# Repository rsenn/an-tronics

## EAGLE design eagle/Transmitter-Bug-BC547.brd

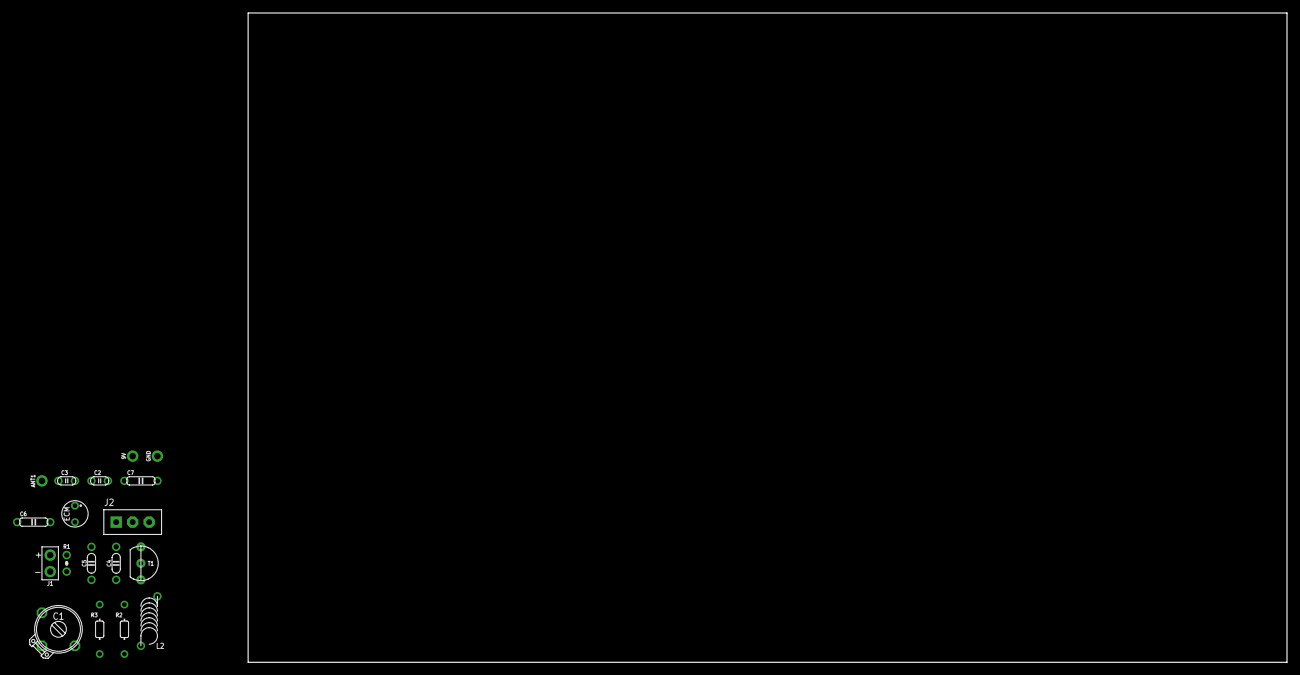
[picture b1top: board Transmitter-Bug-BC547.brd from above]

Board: 2 copper layers, 160.0 x 100.0 mm, 18 parts (0 on the bottom side), 9 nets, no tracks yet.

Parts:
9V: SPAD
ANT1: ANT; SPAD
C1: 1.6-15pF; TRIM-2222-808
C2: 4.7pF; C025-015X024
C3: 1nF; C025-015X024
C4: 1nF; C050-020X036/V
C5: 22nF; C050-020X036/V
C6, C7: 330nF; C050-020X044
ECM: ECM-4
GND: SPAD
J1: SPAD-+
J2: CONN-3P
L2: 1μH; L-04/7V-X
R1: 4.7Ω; 0204/2V
R2: 4.7kΩ; 0202/7-V
R3: 33kΩ; 0202/7-V
T1: BC547; TO92-CBE

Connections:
+UB: 9V.1, C1.3, C5.1, L2.2, R2.1, R3.1
GND: C3.2, C4.2, C5.2, ECM.2, GND.1, J1.1, R1.2
MOD: C4.1, J2.2, R3.2, T1.B
unnamed: C6.2, J2.3
unnamed: ANT1.1, C1.2, C2.1, L2.1, T1.C
unnamed: C2.2, C3.1, R1.1, T1.E
unnamed: C7.2, J2.1
unnamed: C6.1, J1.2
unnamed: C7.1, ECM.1, R2.2

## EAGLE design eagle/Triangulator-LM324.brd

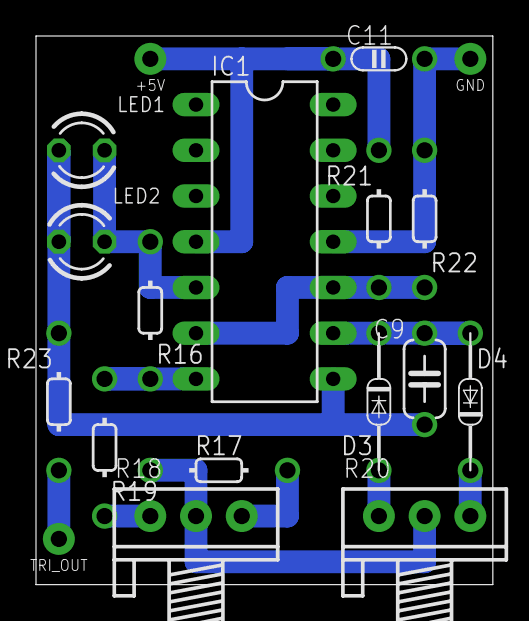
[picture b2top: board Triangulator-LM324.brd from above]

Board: 2 copper layers, 25.4 x 30.5 mm, 18 parts (0 on the bottom side), 13 nets.

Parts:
+5V: VCC; SPAD
C9: 1μF; C050-024X044/V
C11: 100nF; C050-020X036
D3, D4: 1N4148; DO34-7V
GND: GND; SPAD
IC1: LM324; DIL14
LED1, LED2: LED3MM
R16: 47kΩ; 0202/7-V
R17: 4.7kΩ; 0202/7
R18: 10kΩ; POT
R19: 4.7kΩ; 0202/7-V
R20: 100kΩ; POT
R21, R22: 100kΩ; 0202/7-V
R23: 1kΩ; 0202/7-V
TRI_OUT: TRIANGLE; SPAD

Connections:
GND: C11.2, GND.1, IC1.11, R22.1
unnamed: IC1.7, R16.2, R19.1
unnamed: IC1.5, LED1.A, LED2.K, R16.1
unnamed: D3.A, R20.1
unnamed: D4.C, R20.3
unnamed: R17.2, R18.2, R20.2
unnamed: R17.1, R18.3
unnamed: C9.1, D3.C, D4.A, IC1.9
unnamed: R18.1, R19.2
unnamed: C9.2, IC1.8, LED1.K, LED2.A, R23.2
unnamed: R23.1, TRI_OUT.1
unnamed: IC1.6, IC1.10, R21.1, R22.2
VCC: +5V.1, C11.1, IC1.4, R21.2

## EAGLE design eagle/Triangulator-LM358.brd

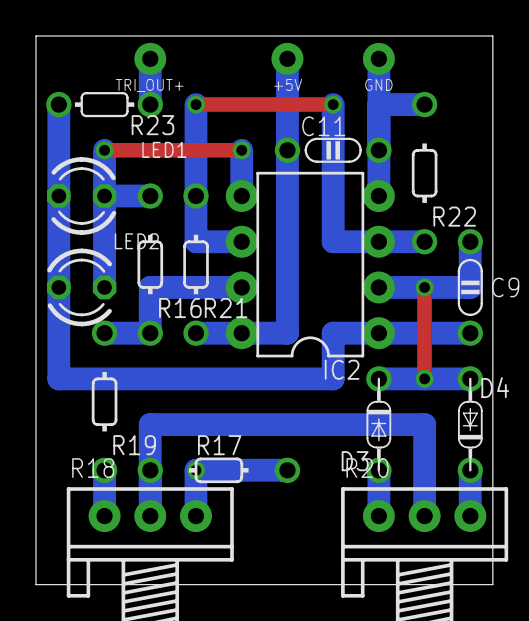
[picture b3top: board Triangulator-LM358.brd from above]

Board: 2 copper layers, 25.4 x 30.5 mm, 18 parts (0 on the bottom side), 13 nets.

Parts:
+5V: VCC; SPAD
C9: 1μF; C050-020X036/V
C11: 100nF; C050-020X036
D3, D4: 1N4148; DO34-5V
GND: GND; SPAD
IC2: LM358N; DIL08
LED1, LED2: LED3MM
R16: 47kΩ; 0202/7-V
R17: 4.7kΩ; 0202/7
R18: 10kΩ; POT
R19: 4.7kΩ; 0202/7-V
R20: 100kΩ; POT
R21, R22: 100kΩ; 0202/7-V
R23: 1kΩ; 0202/5
TRI_OUT+: TRIANGLE; SPAD

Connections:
GND: C11.2, GND.1, IC2.4, R22.1
unnamed: IC2.7, R16.2, R19.1
unnamed: IC2.5, LED1.A, LED2.K, R16.1
unnamed: D3.A, R20.1
unnamed: D4.C, R20.3
unnamed: R17.2, R18.2, R20.2
unnamed: R17.1, R18.3
unnamed: C9.1, D3.C, D4.A, IC2.2
unnamed: R18.1, R19.2
unnamed: C9.2, IC2.1, LED1.K, LED2.A, R23.2
unnamed: R23.1, TRI_OUT+.1
unnamed: IC2.3, IC2.6, R21.1, R22.2
VCC: +5V.1, C11.1, IC2.8, R21.2

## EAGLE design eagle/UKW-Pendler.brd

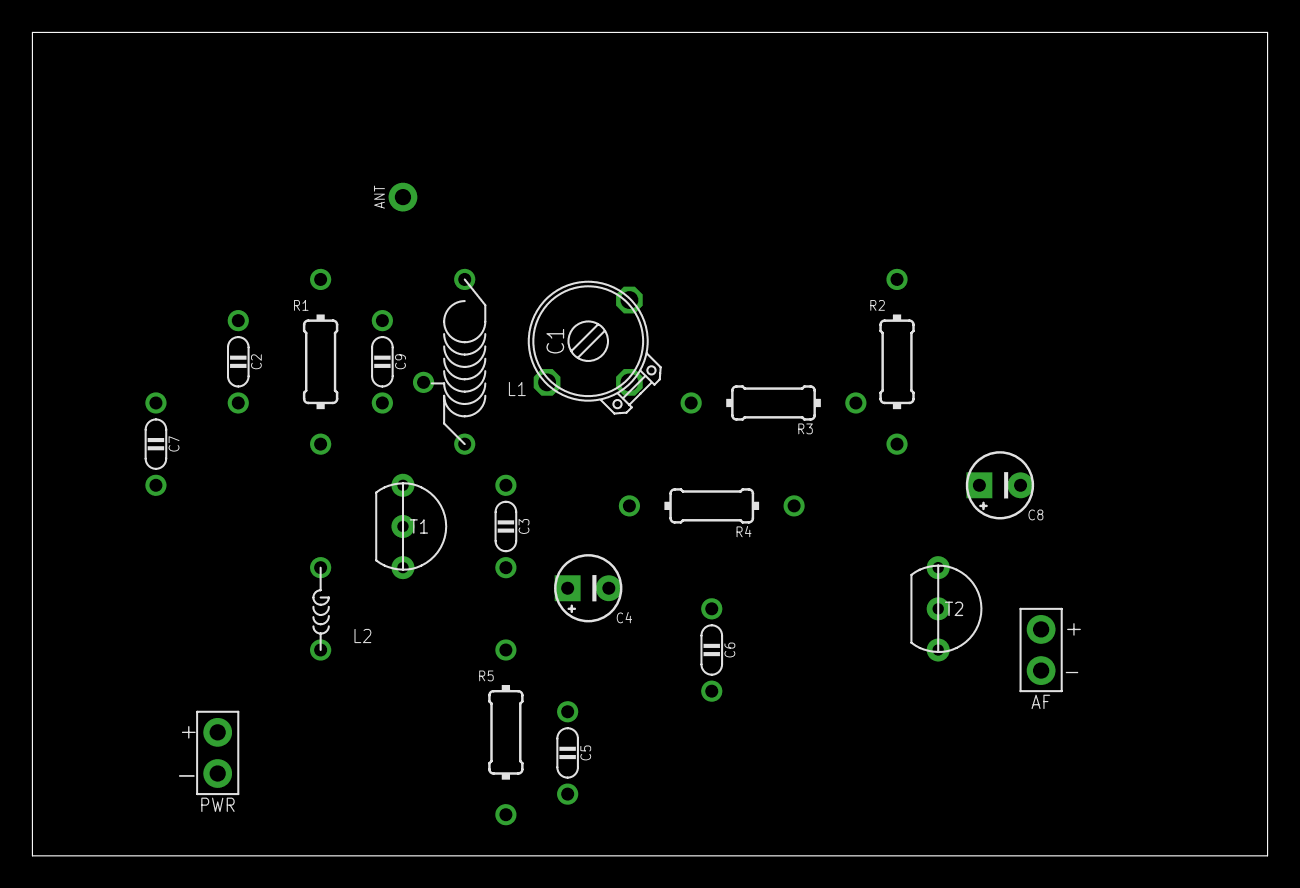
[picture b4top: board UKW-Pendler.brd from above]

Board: 2 copper layers, 76.2 x 50.8 mm, 21 parts (0 on the bottom side), 12 nets, no tracks yet.

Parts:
AF: SPAD+-+-; SPAD+-
ANT: ANT; SPAD
C1: 5-15pF; TRIM-2222-808
C2: 1nF; C050-020X036/V
C3, C5: 27pF; C050-020X036/V
C4: 0.22uF; E2,5-4
C6: 100nF; C050-020X036/V
C7: 10nF; C050-020X036/V
C8: 10uF; E2,5-4
C9: 10pF; C050-020X036/V
J1: PWR-L
L1: L-04/7-TAP1
L2: 4.7uH; L-02/5V
R1: 68k; 0204/10-V
R2, R5: 1k; 0204/10-V
R3: 1M; 0204/10
R4: 10k; 0204/10
T1, T2: BC548B; TO92-CBE

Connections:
GND: AF.1, C5.2, C6.2, C7.2, J1.1, R5.2, T2.E
unnamed: ANT.1, C9.1
unnamed: C3.2, C4.+, L2.2, T1.E
unnamed: C1.2, C3.1, L1.1, T1.C
unnamed: C4.-, R4.2
unnamed: C6.1, R3.2, R4.1, T2.B
unnamed: C5.1, L2.1, R5.1
unnamed: C2.2, R1.2, T1.B
unnamed: C8.+, R2.2, R3.1, T2.C
unnamed: AF.2, C8.-
unnamed: C9.2, L1.T
unnamed: C1.3, C2.1, C7.1, L1.2, R1.1, R2.1

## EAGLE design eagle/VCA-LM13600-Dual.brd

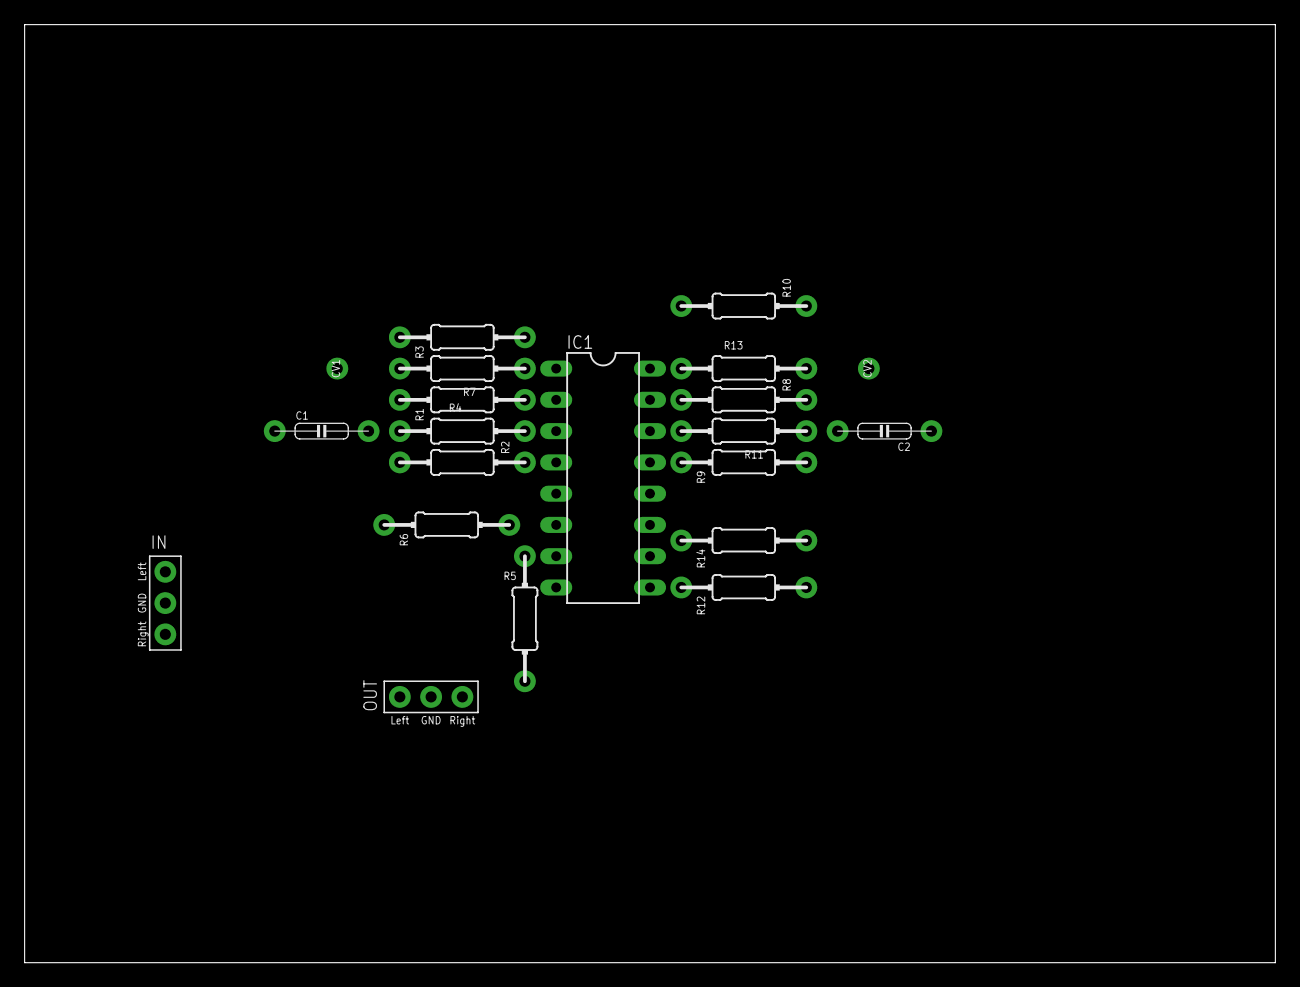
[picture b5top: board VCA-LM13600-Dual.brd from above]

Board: 2 copper layers, 101.6 x 76.2 mm, 21 parts (0 on the bottom side), 21 nets, no tracks yet.

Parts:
C1, C2: 470nF; C075-020X044
CV1, CV2: HPORT; SPAD
IC1: LM13600; DIL16
IN: SAUDIOL-GND-R; SPAD-L-GND-R
OUT: SAUDIOL-GND-R; SPAD-L-GND-R
R1, R8: 10kΩ; 0204/10-V
R2, R3, R9, R10: 470Ω; 0204/10-V
R4, R11: 27kΩ; 0204/10
R5, R12: 33kΩ; 0204/10-V
R6, R14: 4.7kΩ; 0204/10-V
R7, R13: 22kΩ; 0204/10

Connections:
+15V: R1.1, R8.1
-15V: IC1.6, R6.2, R14.2
GND: IN.0, OUT.0, R2.2, R3.1, R5.2, R9.2, R10.1, R12.2
unnamed: IC1.4, R2.1
unnamed: C1.2, R4.1
unnamed: IC1.3, R3.2, R4.2
unnamed: IC1.2, R1.2
unnamed: IC1.1, R7.1
unnamed: IC1.5, IC1.7, R5.1
unnamed: IC1.8, OUT.L, R6.1
unnamed: IC1.13, R9.1
unnamed: IC1.14, R10.2, R11.2
unnamed: IC1.15, R8.2
unnamed: C2.2, R11.1
unnamed: IC1.16, R13.1
unnamed: IC1.9, IC1.12, R12.1
unnamed: IC1.10, OUT.R, R14.1
unnamed: C1.1, IN.L
unnamed: C2.1, IN.R
unnamed: CV1.1, R7.2
unnamed: CV2.1, R13.2

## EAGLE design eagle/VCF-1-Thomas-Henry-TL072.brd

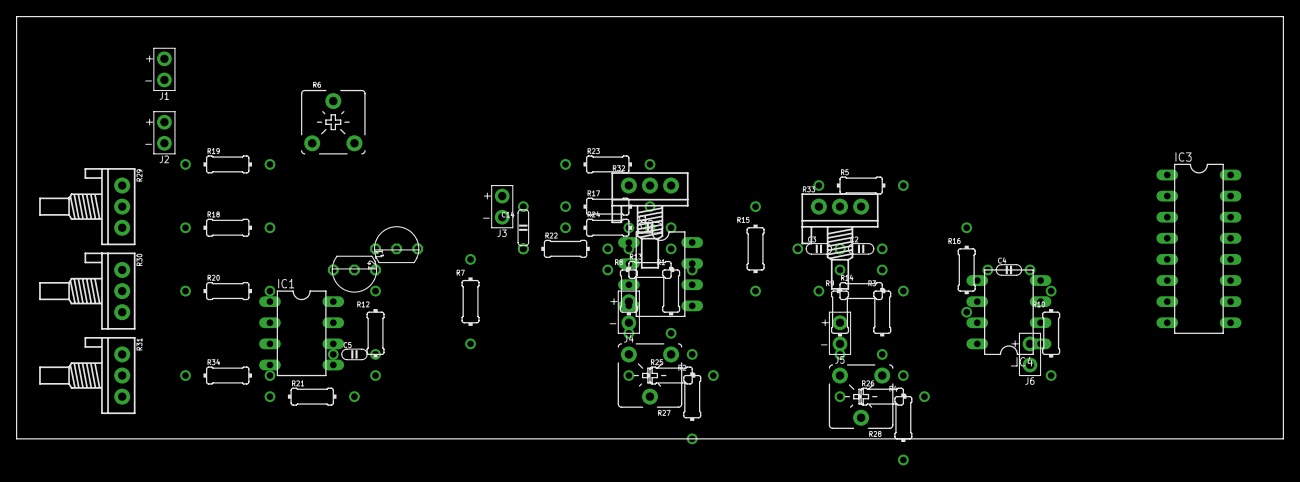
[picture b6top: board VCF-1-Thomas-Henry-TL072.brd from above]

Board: 2 copper layers, 152.4 x 50.8 mm, 51 parts (0 on the bottom side), 38 nets, no tracks yet.

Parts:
C1, C2: 10pF; C050-020X036
C3, C4: 330pF; C050-020X036
C5: 1nF; C050-020X036
C14: 0.22uF; C050-020X044/V
IC1, IC2, IC4: TL072P; DIL08
IC3: LM13600; DIL16
J1: 1V/Oct; SPAD-+
J2: Envelope; SPAD-+
J3, J4, J5, J6: SPAD-+
R1, R2, R3, R4: 22; 0204/10-V
R5: 47; 0204/10
R6, R27, R28: 100; POT-V
R7: 390; 0204/10-V
R8, R9, R10: 1k; 0204/10-V
R12: 5.6k; 0204/10-V
R13, R14: 11k; 0204/10
R15, R16: 15k; 0204/10-V
R17: 27k; 0204/10
R18: 33k; 0204/10
R19, R20, R21, R22, R23, R24, R25, R26: 100k; 0204/10
R29, R30, R31, R33: 100k; POT
R32: POT
R34: 3.3M; 0204/10
T1, T2: 2N3906; TO92

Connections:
GND: IC1.3, IC1.5, IC2.3, IC2.5, IC4.3, J1.1, J2.1, J3.1, J4.1, J5.1, J6.1, R1.2, R2.2, R3.2, R4.2, R5.2, R7.2, R29.1, R32.3, T1.2
IABC: R15.1, R16.1, T2.3
unnamed: J1.2, R19.1
unnamed: R18.1, R29.2
unnamed: J2.2, R29.3
unnamed: R20.1, R30.2
unnamed: R31.2, R34.1
unnamed: IC1.2, R18.2, R19.2, R20.2, R34.2
unnamed: IC1.1, R6.A
unnamed: R6.E, R7.1
unnamed: R12.1, T1.1, T2.1
unnamed: C5.2, IC1.7, R12.2
unnamed: C5.1, IC1.6, R21.2, T1.3
unnamed: R6.S, T2.2
unnamed: R22.1, R32.2
unnamed: IC2.2, R17.1, R22.2, R23.1, R24.1
unnamed: C1.1, IC2.1, R8.1, R13.1, R24.2
unnamed: C1.2, IC3.4, R1.1, R13.2
unnamed: J4.2, R8.2
unnamed: IC3.1, R15.2
unnamed: C3.1, IC2.6, IC3.5
unnamed: C2.1, C3.2, IC2.7, R9.1, R14.1, R33.1
unnamed: J5.2, R9.2
unnamed: C2.2, IC3.13, R3.1, R14.2
unnamed: R25.1, R27.S
unnamed: IC3.3, R2.1, R25.2
unnamed: R26.1, R28.S
unnamed: R4.1, R26.2
unnamed: IC3.16, R16.2
unnamed: C4.1, IC3.12, IC4.2
unnamed: C4.2, IC4.1, R10.1, R23.2
unnamed: J6.2, R10.2
unnamed: R17.2, R33.2
unnamed: R5.1, R33.3
unnamed: C14.1, J3.2
unnamed: C14.2, R32.1
VCC: IC1.8, IC2.8, IC4.8, R27.A, R28.A, R30.1, R31.1
VEE: IC1.4, IC2.4, IC4.4, R21.1, R27.E, R28.E, R30.3, R31.3

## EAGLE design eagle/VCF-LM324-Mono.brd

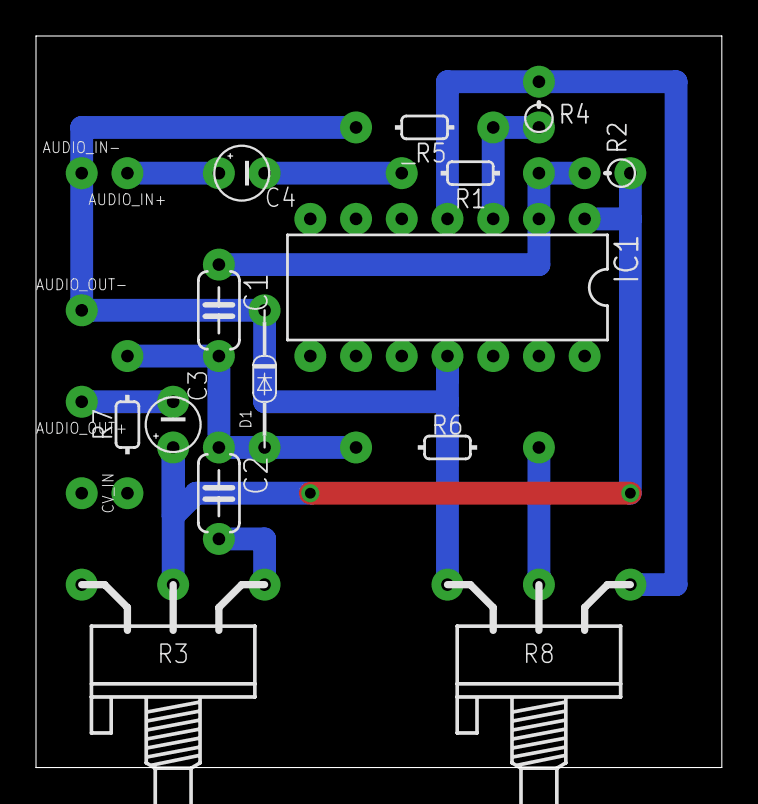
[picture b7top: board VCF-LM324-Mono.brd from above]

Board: 2 copper layers, 38.1 x 40.6 mm, 19 parts (0 on the bottom side), 12 nets.

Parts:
AUDIO_IN+: AUDIO_IN; SPAD
AUDIO_IN-: SPAD
AUDIO_OUT+: AUDIO_OUT; SPAD
AUDIO_OUT-: SPAD
C1, C2: 100nF; C050-024X044
C3, C4: 1μF; E2,5-3
CV_IN: CV_IN; SPAD
D1: 1N4148; DO34-7
IC1: LM324; DIL14
R1: 470kΩ; 0202/7
R2, R4: 100kΩ; 0202V
R3: 10kΩ; POT-P5
R6: 1kΩ; 0202/10
R7: 1kΩ; 0202/7
R8: 100kΩ; POT-P5
_R5: 100kΩ; 0202/7

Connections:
GND: AUDIO_IN-.1, AUDIO_OUT-.1, D1.C, IC1.11, R8.A, _R5.1
unnamed: AUDIO_IN+.1, C4.+
unnamed: C1.1, IC1.2, R1.2, R2.1
unnamed: C2.2, R3.E
unnamed: C3.+, IC1.1, R2.2, R3.S
unnamed: R6.2, R8.S
unnamed: AUDIO_OUT+.1, C3.-
unnamed: IC1.3, R4.2, _R5.2
unnamed: CV_IN.1, R7.2
unnamed: C1.2, C2.1, D1.A, R6.1, R7.1
unnamed: C4.-, R1.1
VCC: IC1.4, R4.1, R8.E
